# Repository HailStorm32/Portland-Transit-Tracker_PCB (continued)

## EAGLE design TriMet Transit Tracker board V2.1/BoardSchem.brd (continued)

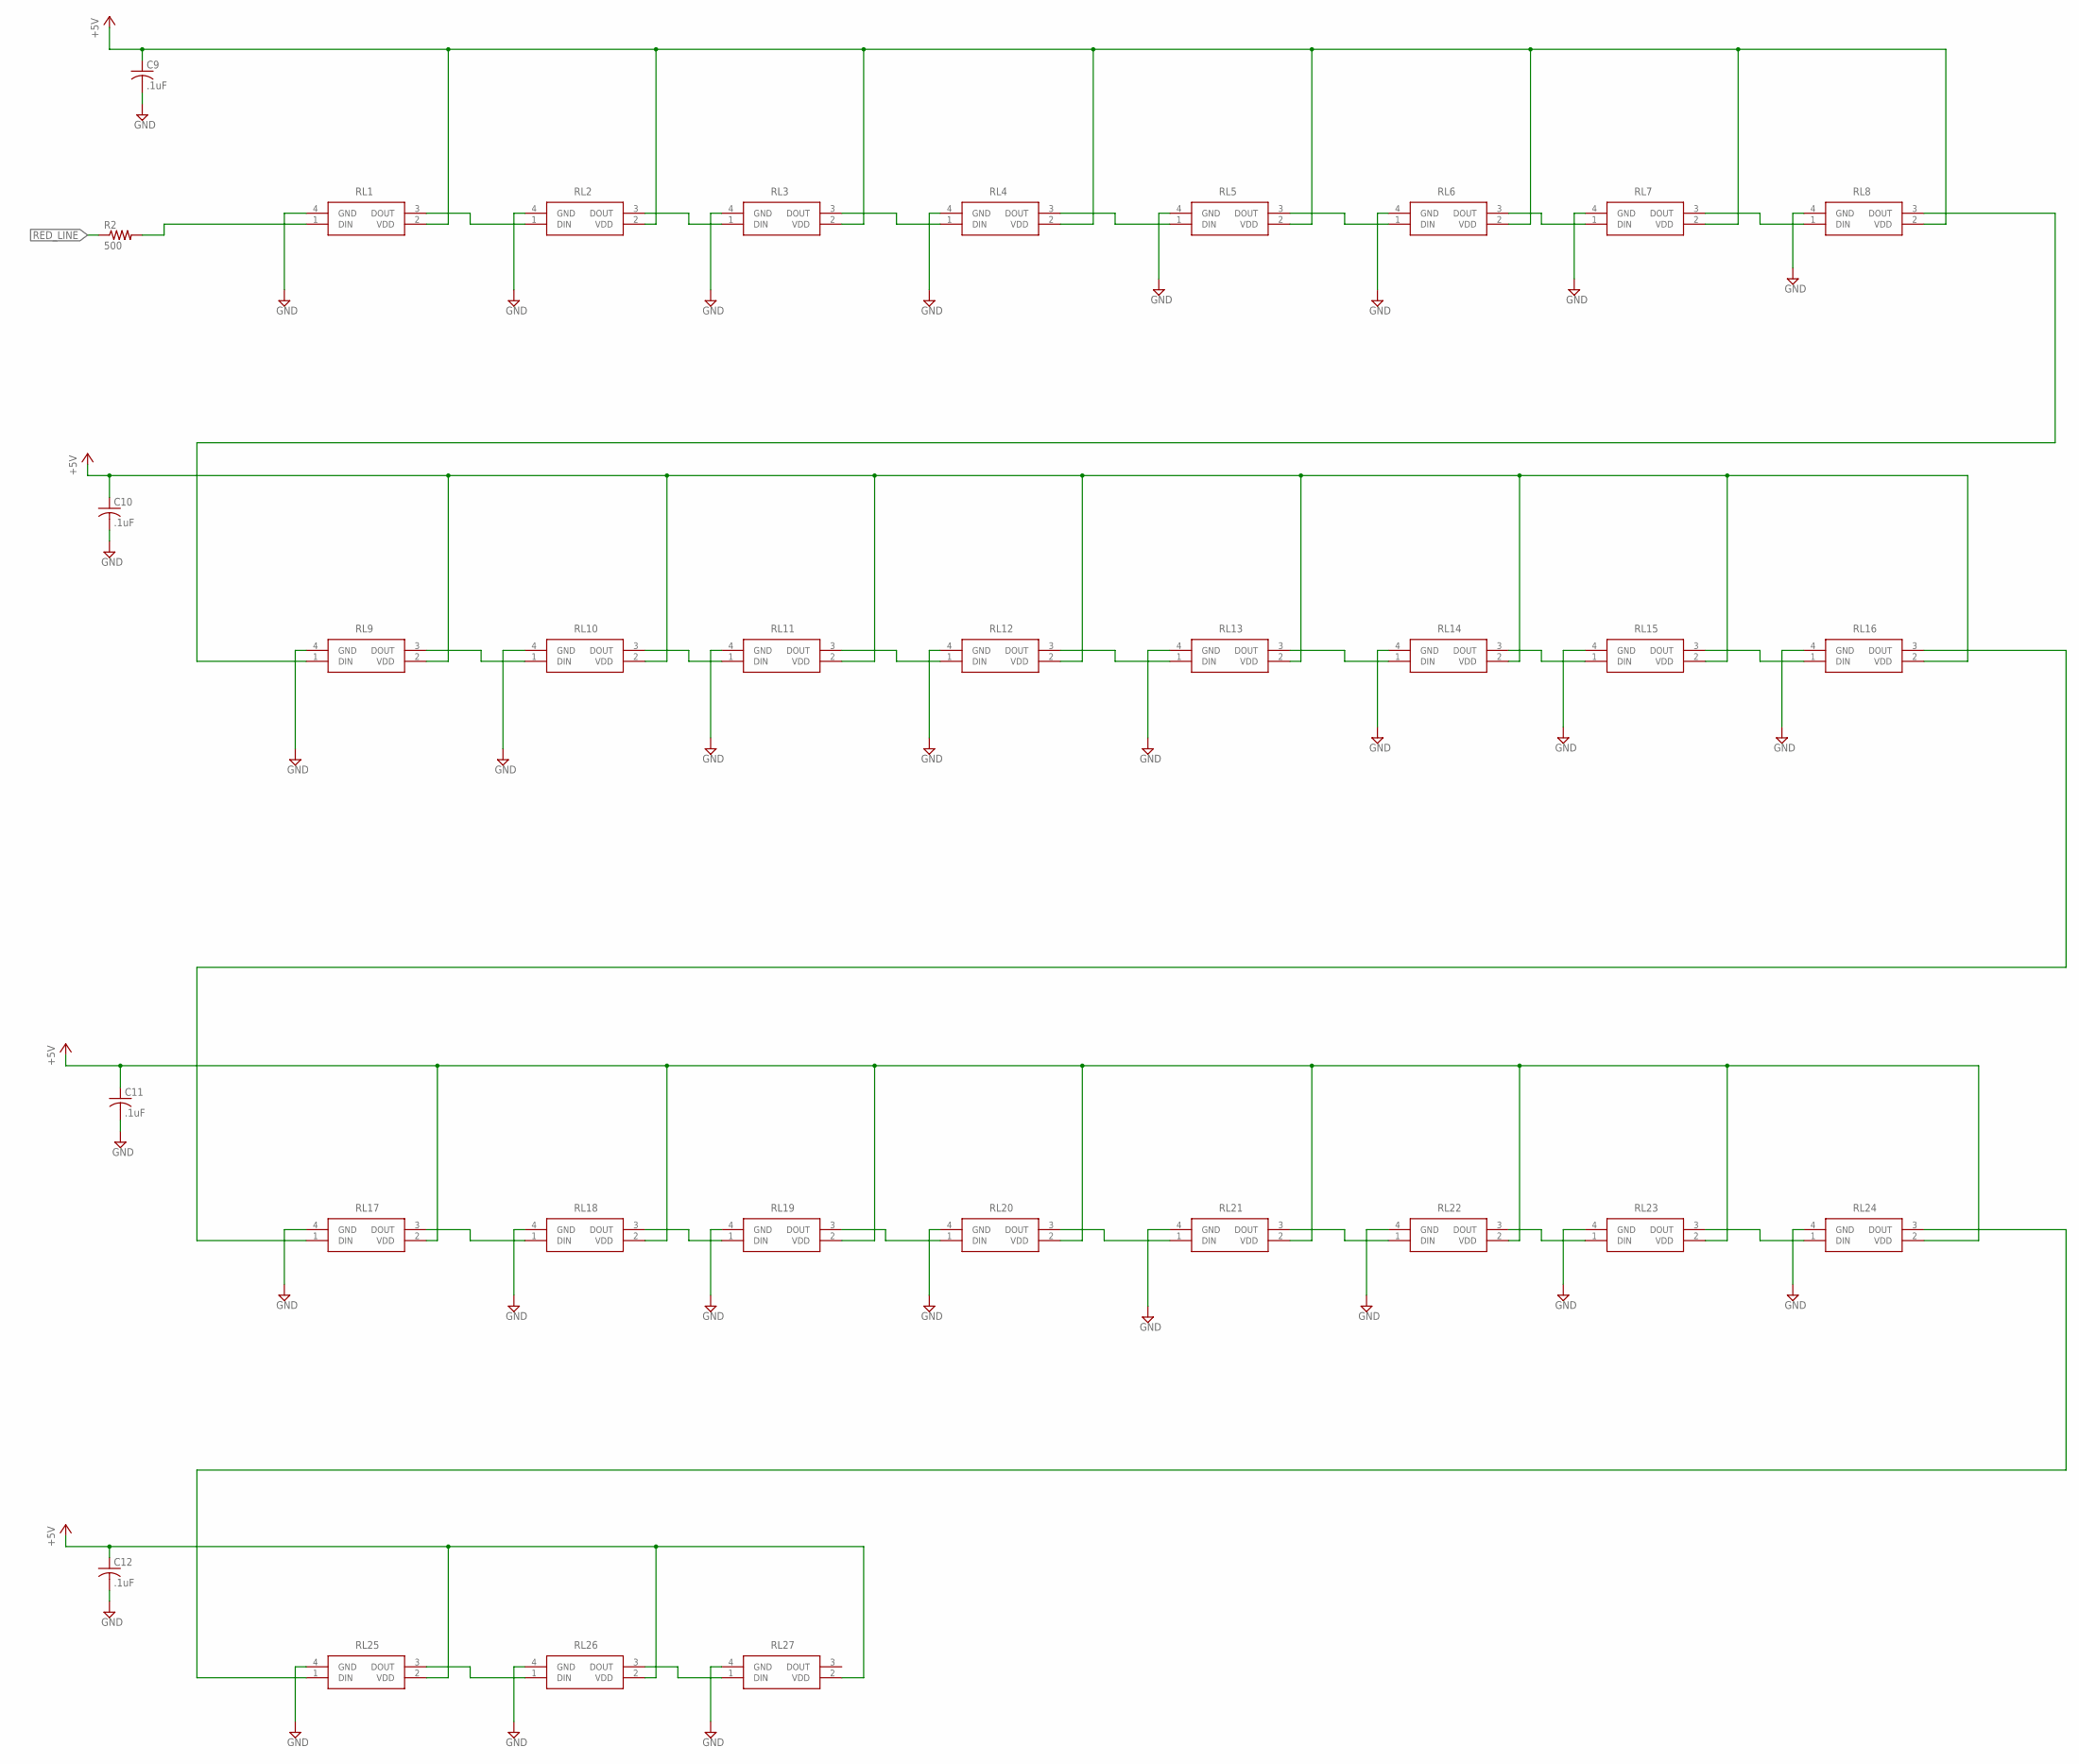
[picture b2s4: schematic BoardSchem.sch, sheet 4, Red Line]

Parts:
C9, C10, C11, C12: .1uF; C0805
R2: 500; R0805
RL1, RL2, RL3, RL4, RL5, RL6, RL7, RL8, RL9, RL10, RL11, RL12, RL13, RL14, RL15, RL16, RL17, RL18, RL19, RL20, RL21, RL22, RL23, RL24, RL25, RL26, RL27: 4492__SK6805-EC_15_; 4492SK6805EC15

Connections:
+5V: C9.1, C10.1, C11.1, C12.1, RL1.2 (VDD), RL2.2 (VDD), RL3.2 (VDD), RL4.2 (VDD), RL5.2 (VDD), RL6.2 (VDD), RL7.2 (VDD), RL8.2 (VDD), RL9.2 (VDD), RL10.2 (VDD), RL11.2 (VDD), RL12.2 (VDD), RL13.2 (VDD), RL14.2 (VDD), RL15.2 (VDD), RL16.2 (VDD), RL17.2 (VDD), RL18.2 (VDD), RL19.2 (VDD), RL20.2 (VDD), RL21.2 (VDD), RL22.2 (VDD), RL23.2 (VDD), RL24.2 (VDD), RL25.2 (VDD), RL26.2 (VDD), RL27.2 (VDD); also elsewhere on the board
GND: C9.2, C10.2, C11.2, C12.2, RL1.4 (GND), RL2.4 (GND), RL3.4 (GND), RL4.4 (GND), RL5.4 (GND), RL6.4 (GND), RL7.4 (GND), RL8.4 (GND), RL9.4 (GND), RL10.4 (GND), RL11.4 (GND), RL12.4 (GND), RL13.4 (GND), RL14.4 (GND), RL15.4 (GND), RL16.4 (GND), RL17.4 (GND), RL18.4 (GND), RL19.4 (GND), RL20.4 (GND), RL21.4 (GND), RL22.4 (GND), RL23.4 (GND), RL24.4 (GND), RL25.4 (GND), RL26.4 (GND), RL27.4 (GND); also elsewhere on the board
unnamed: RL1.3 (DOUT), RL2.1 (DIN)
unnamed: RL2.3 (DOUT), RL3.1 (DIN)
unnamed: RL3.3 (DOUT), RL4.1 (DIN)
unnamed: RL4.3 (DOUT), RL5.1 (DIN)
unnamed: RL5.3 (DOUT), RL6.1 (DIN)
unnamed: RL6.3 (DOUT), RL7.1 (DIN)
unnamed: RL7.3 (DOUT), RL8.1 (DIN)
unnamed: RL8.3 (DOUT), RL9.1 (DIN)
unnamed: RL9.3 (DOUT), RL10.1 (DIN)
unnamed: RL10.3 (DOUT), RL11.1 (DIN)
unnamed: RL11.3 (DOUT), RL12.1 (DIN)
unnamed: RL12.3 (DOUT), RL13.1 (DIN)
unnamed: RL13.3 (DOUT), RL14.1 (DIN)
unnamed: RL14.3 (DOUT), RL15.1 (DIN)
unnamed: RL15.3 (DOUT), RL16.1 (DIN)
unnamed: RL16.3 (DOUT), RL17.1 (DIN)
unnamed: RL17.3 (DOUT), RL18.1 (DIN)
unnamed: RL18.3 (DOUT), RL19.1 (DIN)
unnamed: RL19.3 (DOUT), RL20.1 (DIN)
unnamed: RL20.3 (DOUT), RL21.1 (DIN)
unnamed: RL21.3 (DOUT), RL22.1 (DIN)
unnamed: RL22.3 (DOUT), RL23.1 (DIN)
unnamed: RL23.3 (DOUT), RL24.1 (DIN)
unnamed: RL25.3 (DOUT), RL26.1 (DIN)
unnamed: RL26.3 (DOUT), RL27.1 (DIN)
unnamed: RL24.3 (DOUT), RL25.1 (DIN)
unnamed: R2.2, RL1.1 (DIN)
RED_LINE: R2.1; also elsewhere on the board

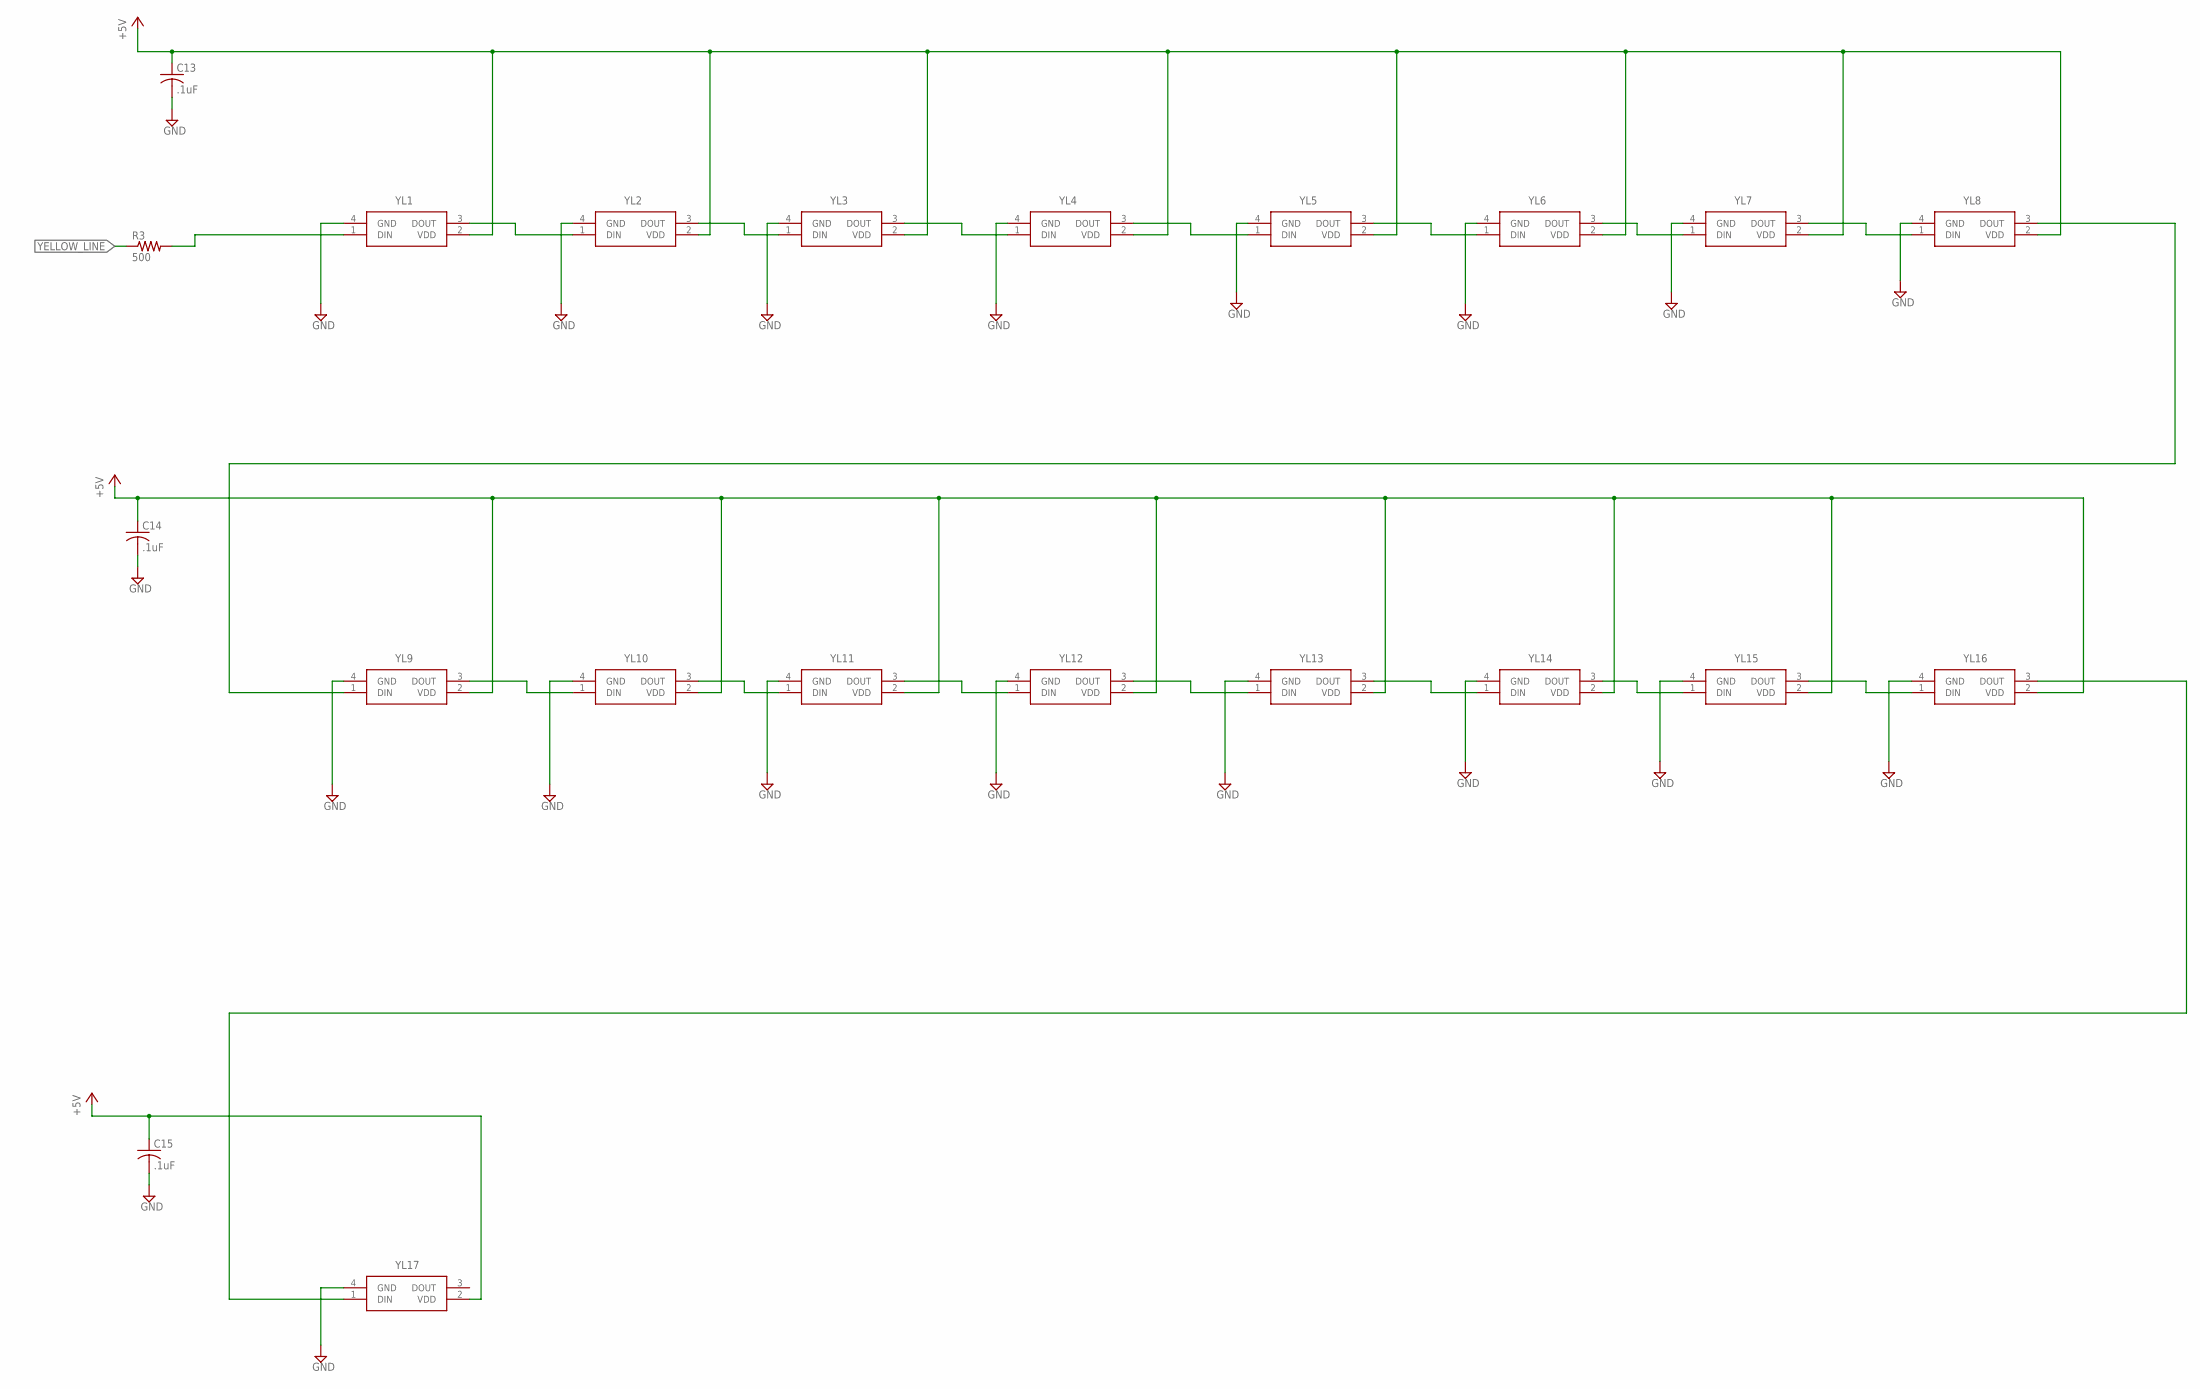
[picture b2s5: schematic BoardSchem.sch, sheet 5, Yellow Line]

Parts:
C13, C14, C15: .1uF; C0805
R3: 500; R0805
YL1, YL2, YL3, YL4, YL5, YL6, YL7, YL8, YL9, YL10, YL11, YL12, YL13, YL14, YL15, YL16, YL17: 4492__SK6805-EC_15_; 4492SK6805EC15

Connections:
+5V: C13.1, C14.1, C15.1, YL1.2 (VDD), YL2.2 (VDD), YL3.2 (VDD), YL4.2 (VDD), YL5.2 (VDD), YL6.2 (VDD), YL7.2 (VDD), YL8.2 (VDD), YL9.2 (VDD), YL10.2 (VDD), YL11.2 (VDD), YL12.2 (VDD), YL13.2 (VDD), YL14.2 (VDD), YL15.2 (VDD), YL16.2 (VDD), YL17.2 (VDD); also elsewhere on the board
GND: C13.2, C14.2, C15.2, YL1.4 (GND), YL2.4 (GND), YL3.4 (GND), YL4.4 (GND), YL5.4 (GND), YL6.4 (GND), YL7.4 (GND), YL8.4 (GND), YL9.4 (GND), YL10.4 (GND), YL11.4 (GND), YL12.4 (GND), YL13.4 (GND), YL14.4 (GND), YL15.4 (GND), YL16.4 (GND), YL17.4 (GND); also elsewhere on the board
unnamed: YL1.3 (DOUT), YL2.1 (DIN)
unnamed: YL2.3 (DOUT), YL3.1 (DIN)
unnamed: YL3.3 (DOUT), YL4.1 (DIN)
unnamed: YL4.3 (DOUT), YL5.1 (DIN)
unnamed: YL5.3 (DOUT), YL6.1 (DIN)
unnamed: YL6.3 (DOUT), YL7.1 (DIN)
unnamed: YL7.3 (DOUT), YL8.1 (DIN)
unnamed: YL8.3 (DOUT), YL9.1 (DIN)
unnamed: YL9.3 (DOUT), YL10.1 (DIN)
unnamed: YL10.3 (DOUT), YL11.1 (DIN)
unnamed: YL11.3 (DOUT), YL12.1 (DIN)
unnamed: YL12.3 (DOUT), YL13.1 (DIN)
unnamed: YL13.3 (DOUT), YL14.1 (DIN)
unnamed: YL14.3 (DOUT), YL15.1 (DIN)
unnamed: YL15.3 (DOUT), YL16.1 (DIN)
unnamed: YL16.3 (DOUT), YL17.1 (DIN)
unnamed: R3.2, YL1.1 (DIN)
YELLOW_LINE: R3.1; also elsewhere on the board

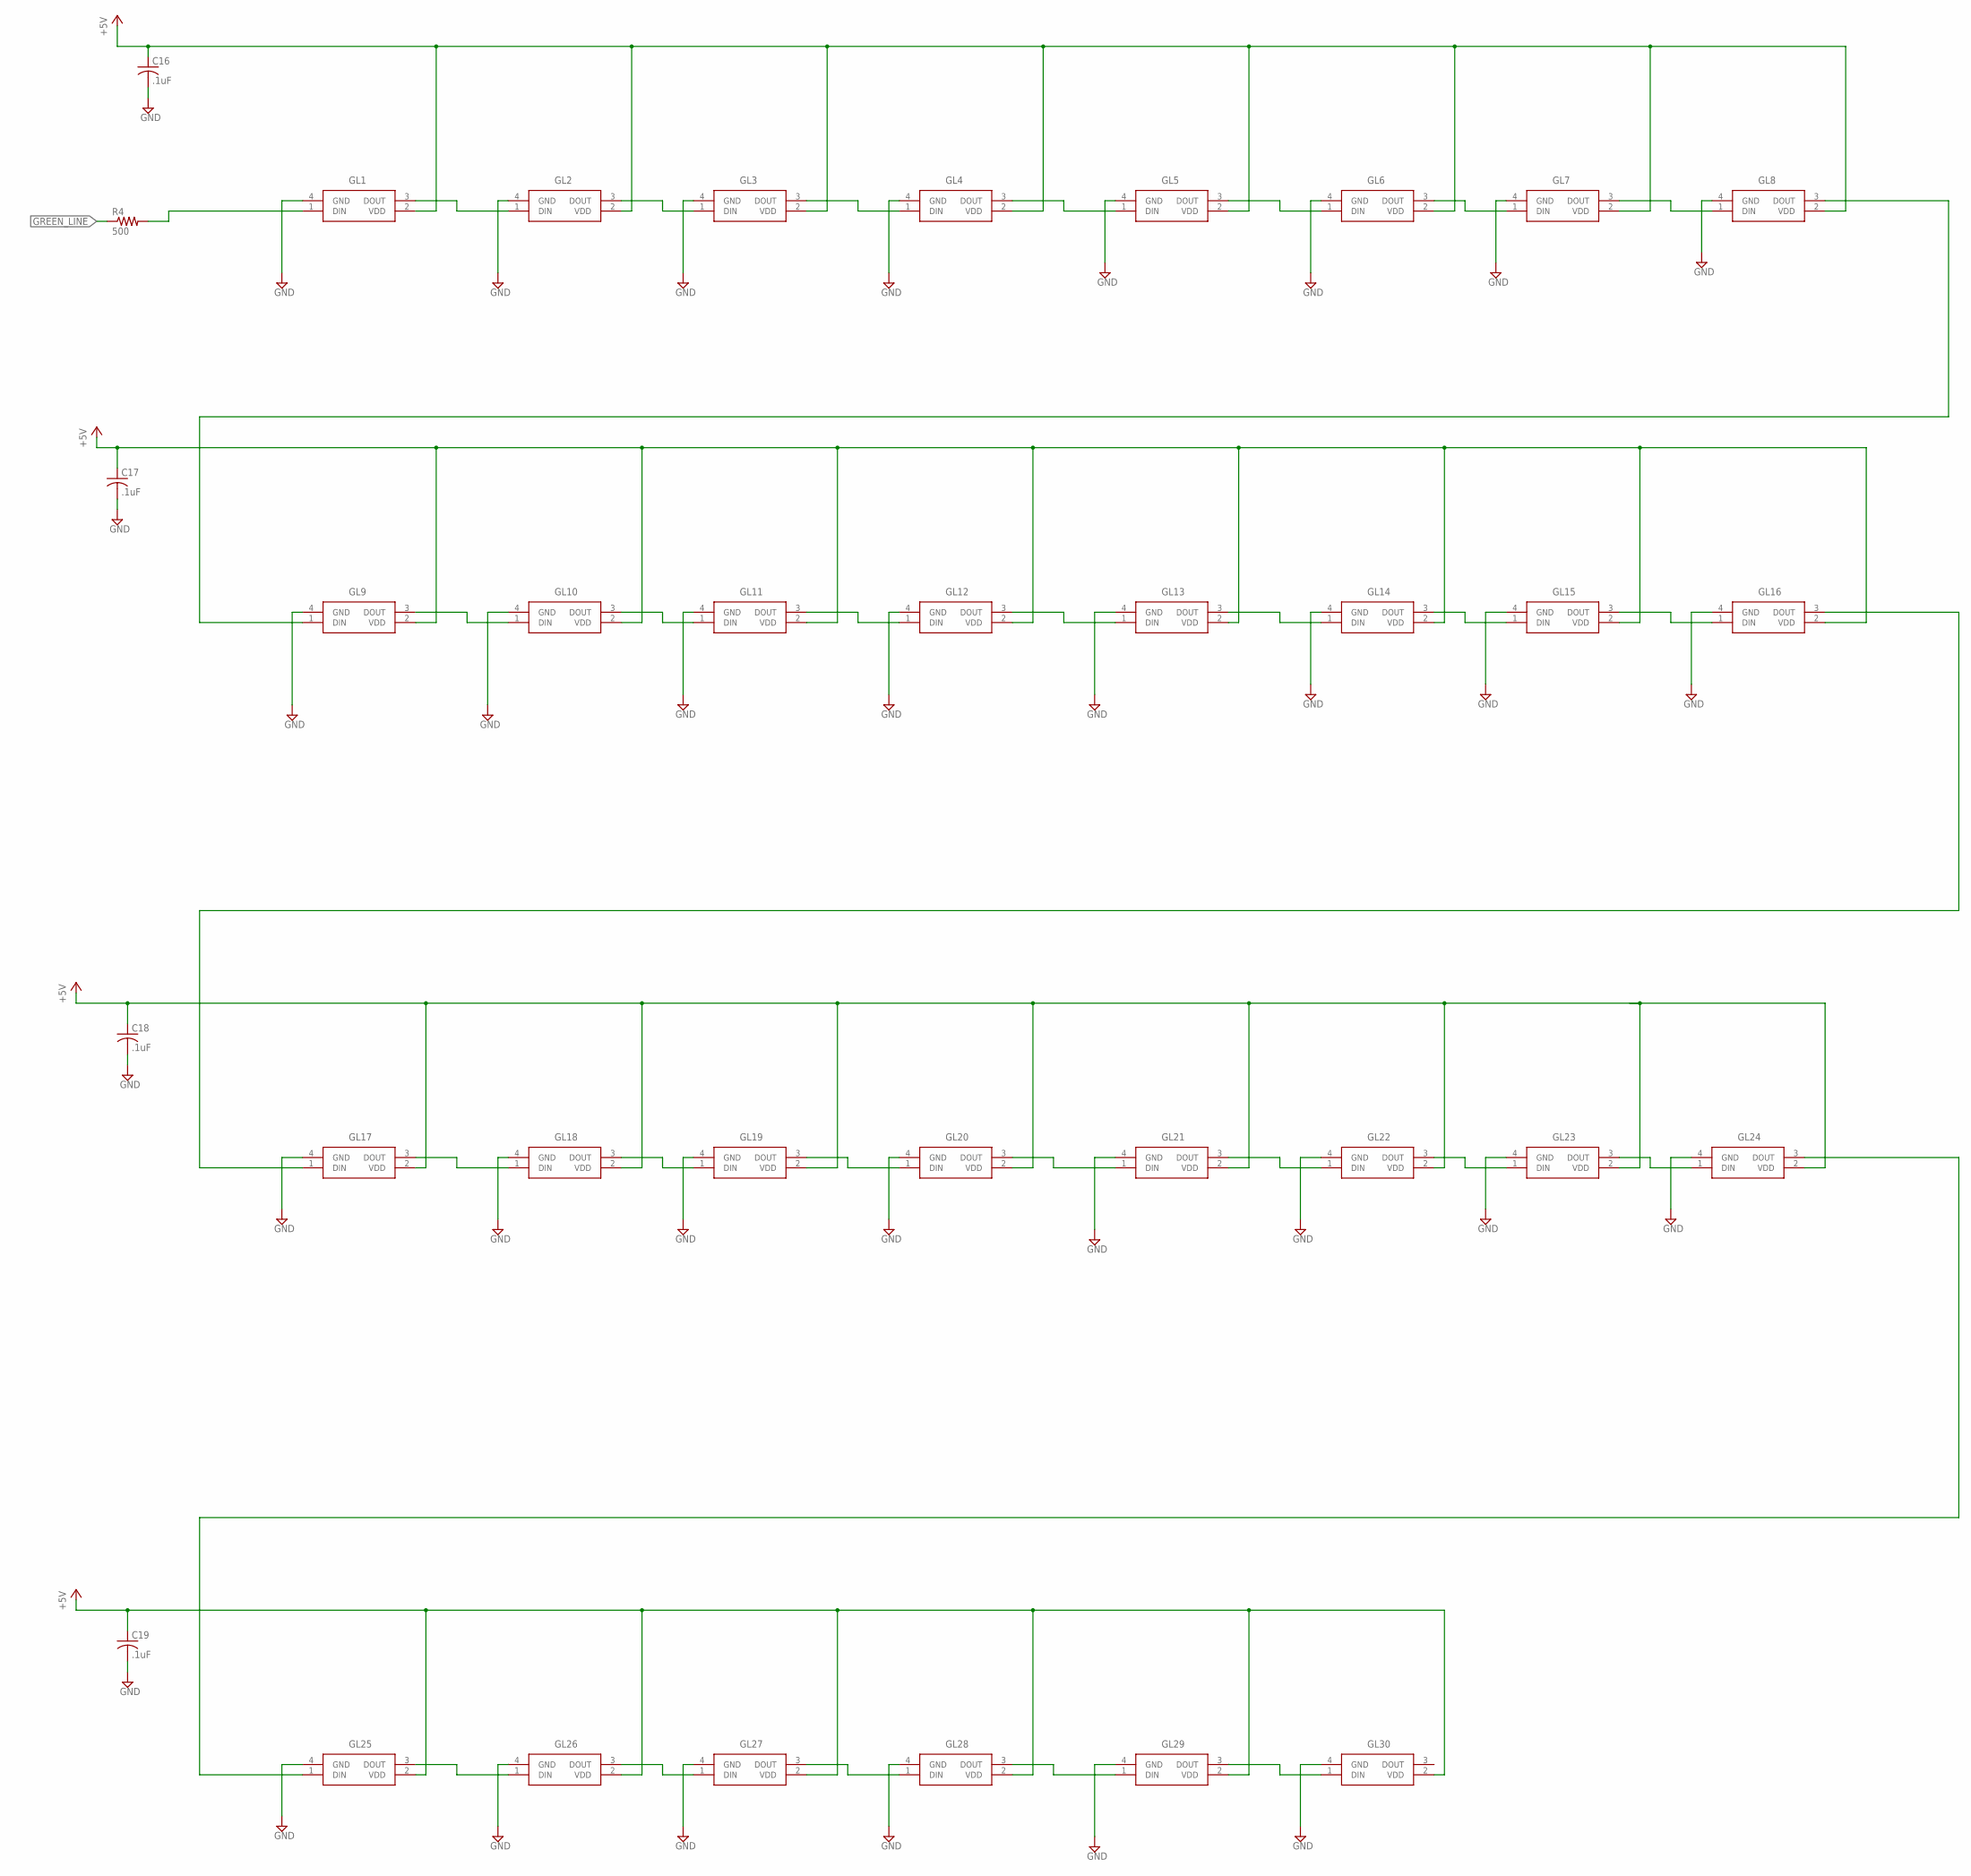
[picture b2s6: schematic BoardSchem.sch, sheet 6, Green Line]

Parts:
C16, C17, C18, C19: .1uF; C0805
GL1, GL2, GL3, GL4, GL5, GL6, GL7, GL8, GL9, GL10, GL11, GL12, GL13, GL14, GL15, GL16, GL17, GL18, GL19, GL20, GL21, GL22, GL23, GL24, GL25, GL26, GL27, GL28, GL29, GL30: 4492__SK6805-EC_15_; 4492SK6805EC15
R4: 500; R0805

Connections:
+5V: C16.1, C17.1, C18.1, C19.1, GL1.2 (VDD), GL2.2 (VDD), GL3.2 (VDD), GL4.2 (VDD), GL5.2 (VDD), GL6.2 (VDD), GL7.2 (VDD), GL8.2 (VDD), GL9.2 (VDD), GL10.2 (VDD), GL11.2 (VDD), GL12.2 (VDD), GL13.2 (VDD), GL14.2 (VDD), GL15.2 (VDD), GL16.2 (VDD), GL17.2 (VDD), GL18.2 (VDD), GL19.2 (VDD), GL20.2 (VDD), GL21.2 (VDD), GL22.2 (VDD), GL23.2 (VDD), GL24.2 (VDD), GL25.2 (VDD), GL26.2 (VDD), GL27.2 (VDD), GL28.2 (VDD), GL29.2 (VDD), GL30.2 (VDD); also elsewhere on the board
GND: C16.2, C17.2, C18.2, C19.2, GL1.4 (GND), GL2.4 (GND), GL3.4 (GND), GL4.4 (GND), GL5.4 (GND), GL6.4 (GND), GL7.4 (GND), GL8.4 (GND), GL9.4 (GND), GL10.4 (GND), GL11.4 (GND), GL12.4 (GND), GL13.4 (GND), GL14.4 (GND), GL15.4 (GND), GL16.4 (GND), GL17.4 (GND), GL18.4 (GND), GL19.4 (GND), GL20.4 (GND), GL21.4 (GND), GL22.4 (GND), GL23.4 (GND), GL24.4 (GND), GL25.4 (GND), GL26.4 (GND), GL27.4 (GND), GL28.4 (GND), GL29.4 (GND), GL30.4 (GND); also elsewhere on the board
GREEN_LINE: R4.1; also elsewhere on the board
unnamed: GL1.3 (DOUT), GL2.1 (DIN)
unnamed: GL2.3 (DOUT), GL3.1 (DIN)
unnamed: GL3.3 (DOUT), GL4.1 (DIN)
unnamed: GL4.3 (DOUT), GL5.1 (DIN)
unnamed: GL5.3 (DOUT), GL6.1 (DIN)
unnamed: GL6.3 (DOUT), GL7.1 (DIN)
unnamed: GL7.3 (DOUT), GL8.1 (DIN)
unnamed: GL8.3 (DOUT), GL9.1 (DIN)
unnamed: GL9.3 (DOUT), GL10.1 (DIN)
unnamed: GL10.3 (DOUT), GL11.1 (DIN)
unnamed: GL11.3 (DOUT), GL12.1 (DIN)
unnamed: GL12.3 (DOUT), GL13.1 (DIN)
unnamed: GL13.3 (DOUT), GL14.1 (DIN)
unnamed: GL14.3 (DOUT), GL15.1 (DIN)
unnamed: GL15.3 (DOUT), GL16.1 (DIN)
unnamed: GL16.3 (DOUT), GL17.1 (DIN)
unnamed: GL17.3 (DOUT), GL18.1 (DIN)
unnamed: GL18.3 (DOUT), GL19.1 (DIN)
unnamed: GL19.3 (DOUT), GL20.1 (DIN)
unnamed: GL20.3 (DOUT), GL21.1 (DIN)
unnamed: GL21.3 (DOUT), GL22.1 (DIN)
unnamed: GL22.3 (DOUT), GL23.1 (DIN)
unnamed: GL24.3 (DOUT), GL25.1 (DIN)
unnamed: GL25.3 (DOUT), GL26.1 (DIN)
unnamed: GL26.3 (DOUT), GL27.1 (DIN)
unnamed: GL27.3 (DOUT), GL28.1 (DIN)
unnamed: GL28.3 (DOUT), GL29.1 (DIN)
unnamed: GL29.3 (DOUT), GL30.1 (DIN)
unnamed: GL23.3 (DOUT), GL24.1 (DIN)
unnamed: GL1.1 (DIN), R4.2

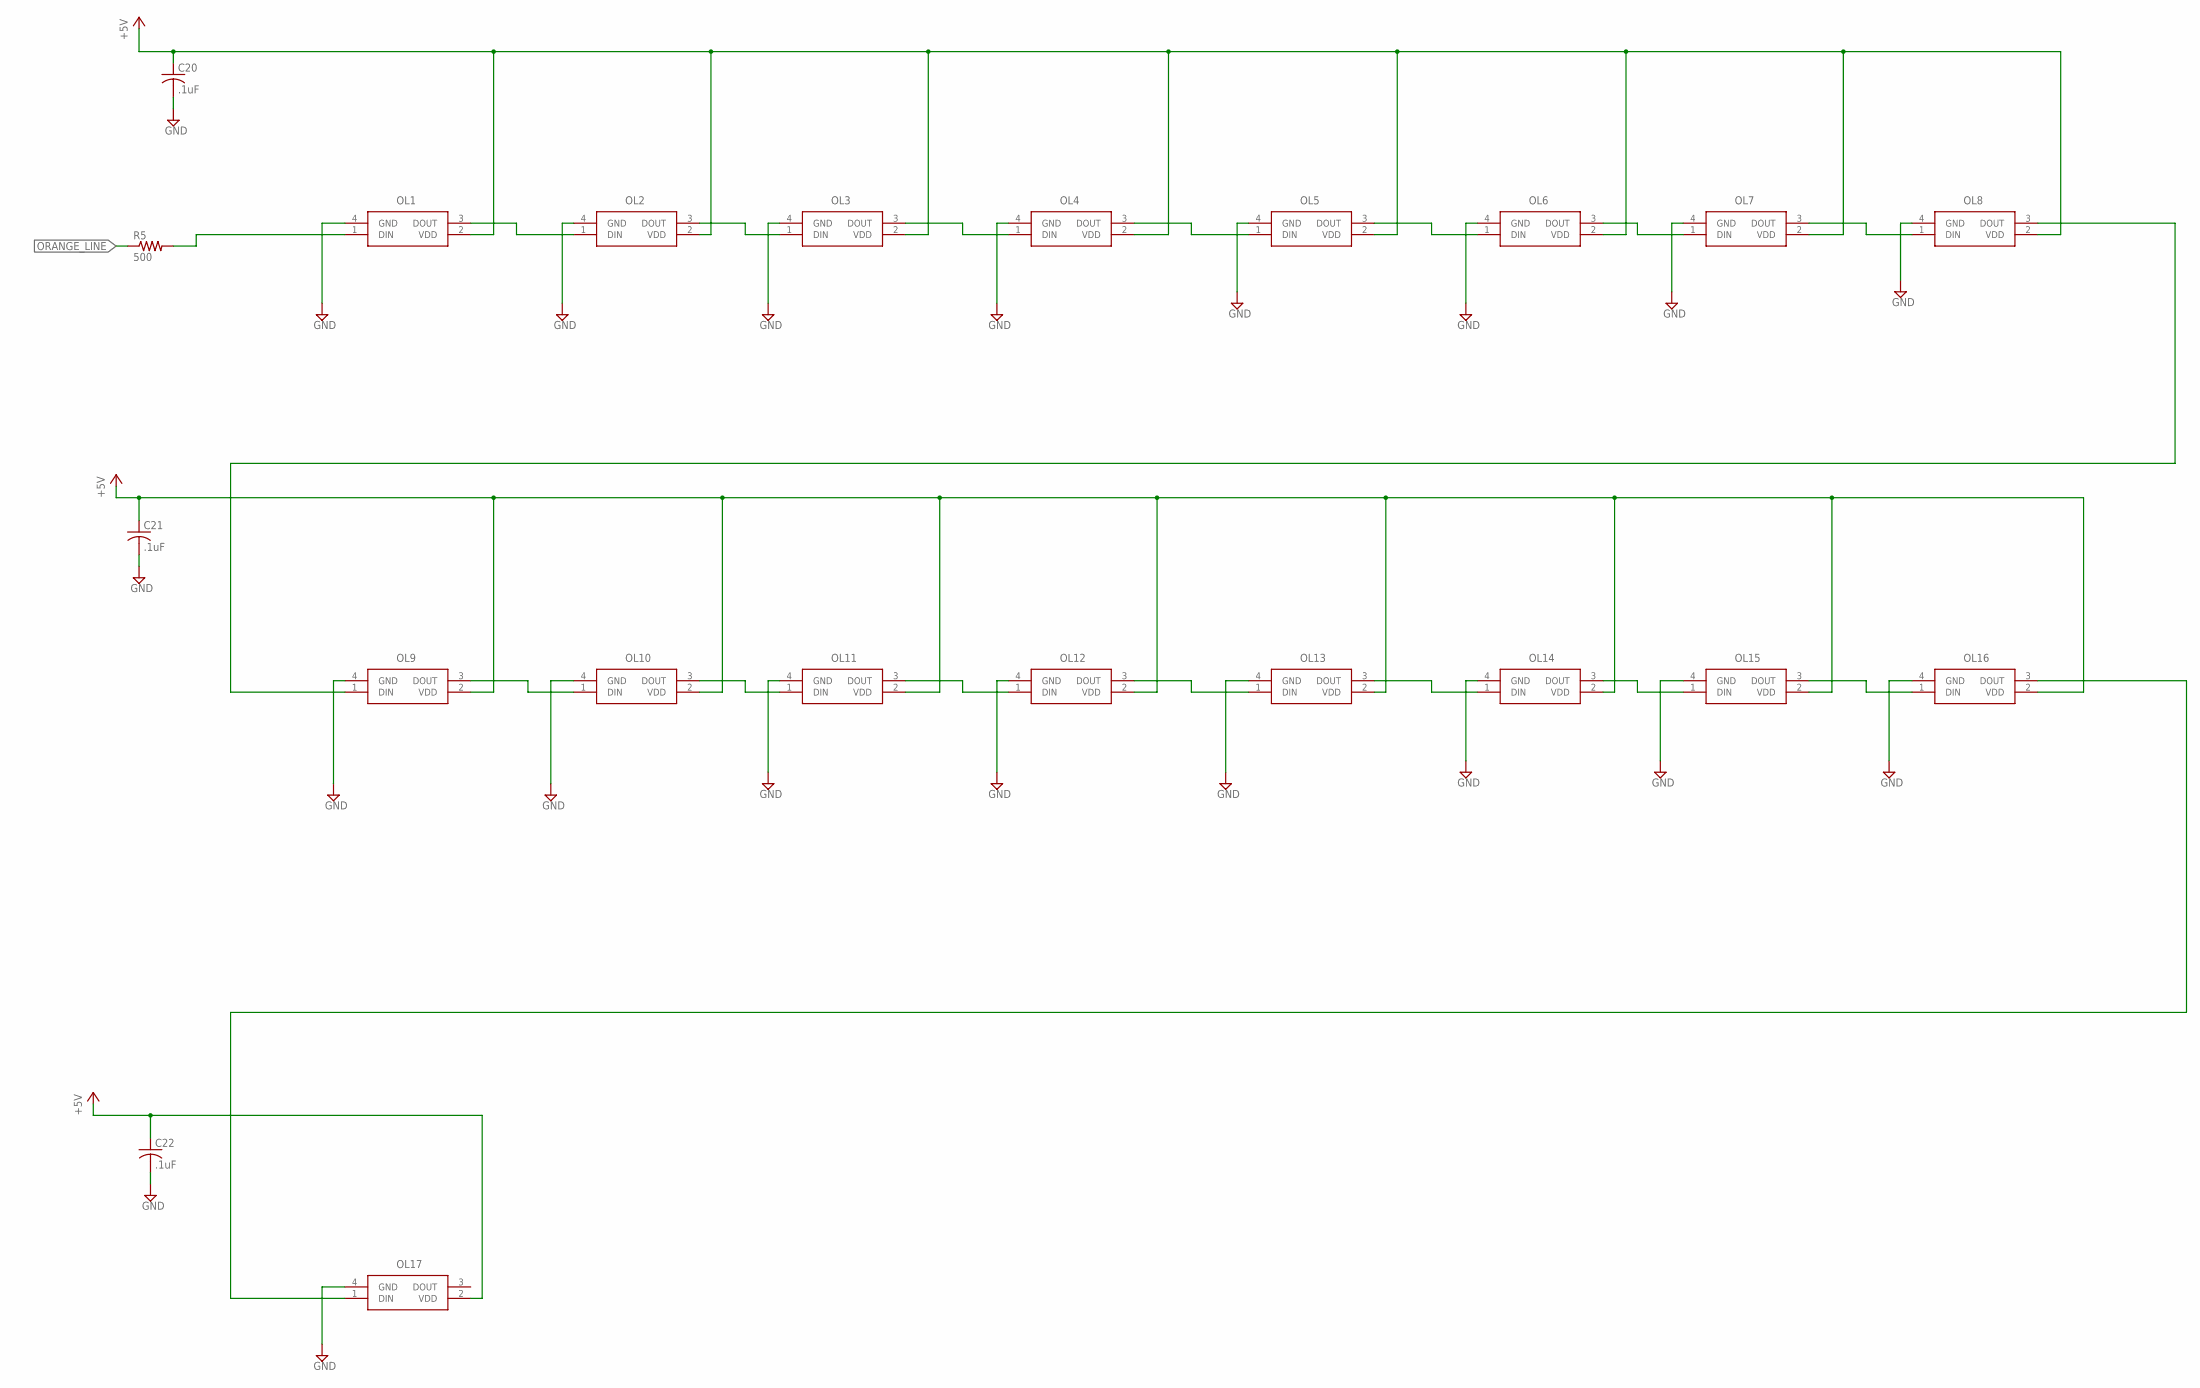
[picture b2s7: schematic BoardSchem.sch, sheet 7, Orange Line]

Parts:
C20, C21, C22: .1uF; C0805
OL1, OL2, OL3, OL4, OL5, OL6, OL7, OL8, OL9, OL10, OL11, OL12, OL13, OL14, OL15, OL16, OL17: 4492__SK6805-EC_15_; 4492SK6805EC15
R5: 500; R0805

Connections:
+5V: C20.1, C21.1, C22.1, OL1.2 (VDD), OL2.2 (VDD), OL3.2 (VDD), OL4.2 (VDD), OL5.2 (VDD), OL6.2 (VDD), OL7.2 (VDD), OL8.2 (VDD), OL9.2 (VDD), OL10.2 (VDD), OL11.2 (VDD), OL12.2 (VDD), OL13.2 (VDD), OL14.2 (VDD), OL15.2 (VDD), OL16.2 (VDD), OL17.2 (VDD); also elsewhere on the board
GND: C20.2, C21.2, C22.2, OL1.4 (GND), OL2.4 (GND), OL3.4 (GND), OL4.4 (GND), OL5.4 (GND), OL6.4 (GND), OL7.4 (GND), OL8.4 (GND), OL9.4 (GND), OL10.4 (GND), OL11.4 (GND), OL12.4 (GND), OL13.4 (GND), OL14.4 (GND), OL15.4 (GND), OL16.4 (GND), OL17.4 (GND); also elsewhere on the board
unnamed: OL1.3 (DOUT), OL2.1 (DIN)
unnamed: OL2.3 (DOUT), OL3.1 (DIN)
unnamed: OL3.3 (DOUT), OL4.1 (DIN)
unnamed: OL4.3 (DOUT), OL5.1 (DIN)
unnamed: OL5.3 (DOUT), OL6.1 (DIN)
unnamed: OL6.3 (DOUT), OL7.1 (DIN)
unnamed: OL7.3 (DOUT), OL8.1 (DIN)
unnamed: OL8.3 (DOUT), OL9.1 (DIN)
unnamed: OL9.3 (DOUT), OL10.1 (DIN)
unnamed: OL10.3 (DOUT), OL11.1 (DIN)
unnamed: OL11.3 (DOUT), OL12.1 (DIN)
unnamed: OL12.3 (DOUT), OL13.1 (DIN)
unnamed: OL13.3 (DOUT), OL14.1 (DIN)
unnamed: OL14.3 (DOUT), OL15.1 (DIN)
unnamed: OL15.3 (DOUT), OL16.1 (DIN)
unnamed: OL16.3 (DOUT), OL17.1 (DIN)
unnamed: OL1.1 (DIN), R5.2
ORANGE_LINE: R5.1; also elsewhere on the board

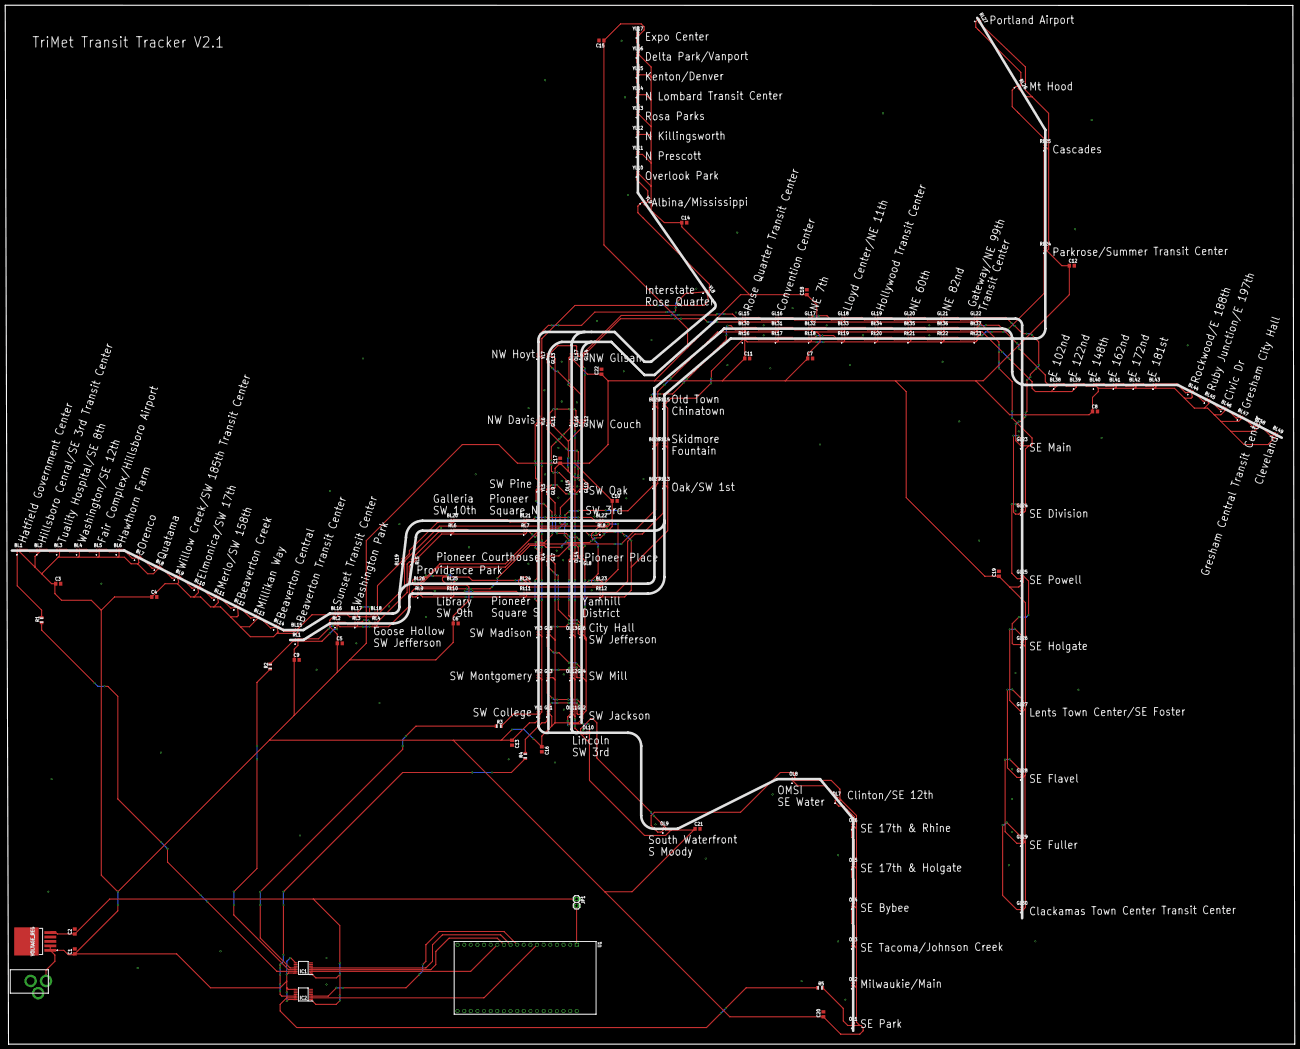
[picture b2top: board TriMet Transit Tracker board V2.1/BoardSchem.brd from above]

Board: 2 copper layers, 494.4 x 398.3 mm, 173 parts (0 on the bottom side), 154 nets.

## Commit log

2021-08-31 inital commit
2021-09-09 Added README
